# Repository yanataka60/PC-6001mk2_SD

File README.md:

# PC-6001mk2 MODE1～MODE4にSD-CARDからロード、セーブ機能

　PC-6001mk2の MODE1～MODE4でSD-CARDからロード、セーブ機能を実現するものです。

　対応機種は、PC-6001mk2、PC-6001mk2SR、PC-6601、PC-6601SRです。PC-6601、PC-6601SRはドライブ数切替スイッチは0として使ってください。

　対応しているCMT形式は、P6形式(拡張子はP6、CASのどちらでも大丈夫)とP6T形式です。

　CMTからの読み込み実行に数分掛かっていたゲームも数十秒で実行できます。

　なお、Arduino、ROMへ書き込むための機器が別途必要となります。

　また、本体内のBASIC-ROMを差し替えられるスキルがあればMODE5もSD対応にできます。詳細は、「MODE5対応について」を参照してください。

## 対応できないもの
　MODE1～MODE4については、BASIC-ROMを裏RAMにコピーしCMT関連ルーチンをSD-CARDアクセスに書き換えてSD-CARDへのアクセスを実現しています。

　MODE5についてはBASIC-ROMのCMT関連ルーチンにパッチを当てたROMに差し替えることでSD-CARDへのアクセスを実現していますが、MODE6についてはBASIC-ROMのCMT関連ルーチンが特定できていないためSD-CARDは使えません。

　また、BASIC-ROMのCMT関連ルーチンをコールせず独自ルーチンによりCMTからLOADするソフト（ロードランナー等）も対応できないので途中で止まります。

## 回路図
　KiCadフォルダ内のPC-6001mk2_SD.pdfを参照してください。

[回路図](https://github.com/yanataka60/PC-6001mk2_SD/blob/main/Kicad/PC-6001_mk2_SD.pdf)

## 部品
|番号|品名|数量|備考|
| ------------ | ------------ | ------------ | ------------ |
||J2、J3のいずれか(注1)|||
|J2|Micro_SD_Card_Kit|1|秋月電子通商 AE-microSD-LLCNV (注2)|
|J3|MicroSD Card Adapter|1|Arduino等に使われる5V電源に対応したもの (注4)|
|U1|74LS04|1||
|U2|74LS30|1||
|U4|8255|1||
|U5|2764/28C64相当品|1||
|U6|Arduino_Pro_Mini_5V|1|Atmega328版を使用 168版は不可。(注3)|
|C1 C2 C4 C5|積層セラミックコンデンサ 0.1uF|4||
|C6|電解コンデンサ 16v100uF|1||
||ピンヘッダ|2Pin分|Arduino_Pro_MiniにはA4、A5用のピンヘッダが付いていないため別途調達が必要です 秋月電子通商 PH-1x40SGなど|
||ピンソケット(任意)|26Pin分|Arduino_Pro_Miniを取り外し可能としたい場合に調達します 秋月電子通商 FHU-1x42SGなど|

　　　注1)J2又はJ3のどちらかを選択して取り付けてください。

　　　注2)秋月電子通商　AE-microSD-LLCNVのJ1ジャンパはショートしてください。

　　　注3)Arduino Pro MiniはA4、A5ピンも使っています。

　　　注4)MicroSD Card Adapterを使う場合

　　　　　J3に取り付けます。

　　　　　MicroSD Card Adapterについているピンヘッダを除去してハンダ付けするのが一番確実ですが、J3の穴にMicroSD Card Adapterをぴったりと押しつけ、裏から多めにハンダを流し込むことでハンダ付けをする方法もあります。なお、この方法の時にはしっかりハンダ付けが出来たかテスターで導通を確認しておいた方が安心です。

ハンダ付けに自信のない方はJ2の秋月電子通商　AE-microSD-LLCNVをお使いください。AE-microSD-LLCNVならパワーLED、アクセスLEDが付いています。

## ROMへの書込み
　Z80フォルダ内のEXT_ROM.binをROMライター(TL866II Plus等)を使って2764又は28C64に書き込みます。

## Arduinoプログラム
　Arduino IDEを使ってArduinoフォルダのPC-6001mk2_SDフォルダ内PC-6001mk2_SD.inoを書き込みます。

　SdFatライブラリを使用しているのでArduino IDEメニューのライブラリの管理からライブラリマネージャを立ち上げて「SdFat」をインストールしてください。

　「SdFat」で検索すれば見つかります。「SdFat」と「SdFat - Adafruit Fork」が見つかりますが「SdFat」のほうを使っています。

注)Arduinoを基板に直付けしている場合、Arduinoプログラムを書き込むときは、カートリッジスロットから抜き、74LS04を外したうえで書き込んでください。

## 接続
　カートリッジスロットに挿入します。

　カートリッジスロットへの抜き差しに基板のみでは不便です。

　STLフォルダに基板を載せられるトレイの3Dデータを置いたので出力して使うと便利です。

　PC-6601、PC-6601SRはドライブ数切替スイッチは0として使ってください。

## SD-CARD
　出来れば8GB以下のSDカードを用意してください。

　ArduinoのSdFatライブラリは、SD規格(最大2GB)、SDHC規格(2GB～32GB)に対応していますが、SDXC規格(32GB～2TB)には対応していません。

　また、SDHC規格のSDカードであっても32GB、16GBは相性により動作しないものがあるようです。

　FAT16又はFAT32が認識できます。NTFSは認識できません。

　ルートに置かれた拡張子が「.P6T」又は「.CAS」の形式ファイルのみ認識できます。(以外のファイル、フォルダも表示されますがLOAD実行の対象になりません)

　ファイル名は拡張子を除いて32文字まで、ただし半角カタカナ、及び一部の記号はArduinoが認識しないので使えません。パソコンでファイル名を付けるときはアルファベット、数字および空白でファイル名をつけてください。

　起動直後の画面は横32文字表示です。拡張子を含めて27文字以下にしたほうが画面の乱れません。

## 使い方

起動直後は拡張ROMのプログラムが走り、以下のコマンドが使えます。

### Launcherコマンド
#### 1から4までのいずれかの後に[CR]
次に「How Many Pages?(1-4)」と聞いてくるので画面数を入力すると入力された数字のMODEと画面数でSD対応にして起動します。

#### B[CR]
SD対応せずにBASICを起動します。

[STOP]キーと動作は同じです。

#### [STOP]キー
SD対応せずにBASICを起動します。

B[CR]と動作は同じです。

#### F[CR]又はF 文字列[CR]
文字列を入力せずにF[CR]のみ入力するとSD-CARDルートディレクトリにあるファイルの一覧を表示します。

文字列を付けて入力すればSD-CARDルートディレクトリにあるその文字列から始まるファイルの一覧を表示します。

10件表示したところで指示待ちになるので打ち切るならESC又は↑を入力すると打ち切られ、Bキーで前の10件に戻ります。それ以外のキーで次の10件を表示します。

　行頭に「*L 」を付加して表示してあるので実行したいファイルにカーソルキーを合わせて[CR]キーを押すだけでLOAD可能です。

　LOADの挙動については次のLコマンドの記述を参照してください。

　表示される順番は、登録順となりファイル名アルファベッド順などのソートした順で表示することはできません。

##### 例)
　　F[CR]

　　F S[CR]

　　F SP[CR]

#### L DOSファイル名[CR]
指定したDOSフィル名のファイルをSD-CARDからLOADします。

ファイル名の最後の「.P6T」「.CAS」は有っても無くても構いませんが、無い場合は「.P6T」が指定されたものとみなします。

　例)

　　L TEST.P6T -> DOSファイル名「TEST.P6T」を読み込みます。

　　L TEST.CAS -> DOSファイル名「TEST.CAS」を読み込みます。

　　L TEST -> DOSファイル名「TEST.P6T」を読み込みます。

　選択したファイルが「P6T」形式の場合、設定されたMODEと設定されたPagesで起動したうえで自動実行文字列を実行します。

　選択したファイルが「CAS」形式の場合、「Mode?(1-4)」と聞いてくるのでモードを入力、次に「How Many Pages?(1-4)」と聞いてくるので画面数を入力、最後に「Auto Run?(y/c/n)」と聞いてくるので「y」とすれば起動直後にCLOAD[CR]RUN[CR]が実行され、「c」とすればCLOAD[CR]だけが実行、「n」とすれば何も実行されません。

#### 操作上の注意
　~~「SD-CARD INITIALIZE ERROR」と表示されたときは、SD-CARDをいったん抜き再挿入したうえでArduinoをリセットしてください。~~

　~~SD-CARDにアクセスしていない時に電源が入ったままで SD-CARDを抜いた後、再挿入しSD-CARDにアクセスすると「SD-CARD INITIALIZE ERROR」となる場合があります。再挿入した場合にはSD-CARDにアクセスする前にArduinoを必ずリセットしてください。~~

　~~SD-CARDの抜き差しは電源を切った状態で行うほうがより確実です。~~

　(2024.3.12) SD-CARDにアクセスしていない時に電源が入ったままでSD-CARDを抜くと再度SD-CARDを挿入してもSD-CARDにアクセスできない問題を解消しました。(Arduinoを最新版に書き換えてください)

　再度SD-CARDを挿入した後、Fコマンド、Lコマンド、CLOAD、CSAVE等でSD-CARDに3回ほどアクセスすれば復旧します。

### BASICコマンド
#### CLOAD "DOSファイル名"[CR]
指定したDOSフィル名のBASICプログラムをSD-CARDからLOADします。

ファイル名は6文字以内で必須です。6文字以上入力された場合には7文字以降は無視されます。ファイル名を入力せずにCLOAD[CR]とすると暴走します。

ファイル名の前に"(ダブルコーテーション)は必須ですが、ファイル名の後ろに"(ダブルコーテーション)は有っても無くても構いません。

ファイル名の最後に「.CAS」は必要ありません。「.CAS」が指定されたものとみなします。

　例)

　　CLOAD "TEST" -> DOSファイル名「TEST.CAS」を読み込みます。

　　CLOAD "TESTTEST" -> DOSファイル名「TESTTE.CAS」を読み込みます。

　　CLOAD "TEST.BAS.CMT" -> DOSファイル名「TEST.BA.CMT」を読み込みます。

#### CSAVE "DOSファイル名"[CR]
BASICプログラムを指定したDOSフィル名でSD-CARDに上書きSAVEします。

ファイル名は6文字以内で必須です。6文字以上入力された場合には7文字以降は無視されます。

ファイル名の前に"(ダブルコーテーション)は必須ですが、ファイル名の後ろに"(ダブルコーテーション)は有っても無くても構いません。

ファイル名の最後の「.CAS」は必要ありません。「.CAS」が指定されたものとみなします。

　例)

　　CSAVE "TEST" -> 「TEST.CAS」で保存される。

　　CSAVE "TESTTEST" -> 「TESTTE.CAS」で保存される。

## MODE5対応について(本体BASIC-ROMの差し替えが必要です、自己責任でお願いします)
　MODE5では裏RAMが使われるため、「BASIC-ROMを裏RAMにコピーしCMT関連ルーチンをSD-CARDアクセスに書き換え」が出来ませんのでSD-CARDアクセス用にパッチを当てたBASIC-ROMに差し替えることでMODE5に対応します。

　なお、市販ソフトでは2段目以降のCMTロードはBASIC-ROMを使わずに独自のロードルーチンを使っているものがあり、動かないことが多いです。

　雑誌打ち込みプログラムのロード、セーブ用と割り切ってください。

　また、本体ROMの抜き差し等において本体が故障又はBASIC-ROMが破損しても当方では責任をとれませんので自己責任で行ってください。

　本体BASIC-ROMの本体内の位置及びROM内容の吸出しに関しても自分で解決できる方のみ挑戦願います。

#### 従来MONITORのRコマンド未対応としていましたが、最初に何らかのBASICプログラムが無いと正常に読み込めないのが原因です。
#### 月刊マイコン '85/11月号掲載「サブマリン606」のように最初にCLOAD、次にMON、R-0とするプログラムは正常に読み込めます。
#### 未確認ですが、機械語だけをR-0で読み込むプログラムも最初になんらかのBASICプログラム(10 clearだけでも)をくっつけたp6ファイルに修正すればR-0で読み込み、Gxxxxで実行できると思います。

### Arduinoプログラム
　ArduinoフォルダのPC-6001mk2_SDフォルダ内PC-6001mk2_SD.inoと同じもので動作します。

### ROMへの書込み
　Z80フォルダ内のEXT_ROM.binと同じもので動作します。

### BASIC-ROMへのパッチあて
　以下のアドレスを修正します。

|ADDRESS|修正前|修正後|
| ------------ | ------------ | ------------ |
|1A61|C5 D5 E5|C3 12 58|
|1A70|C5 D5 E5|C3 15 58|
|1AB8|C5 D5 E5|C3 18 58|
|1ACC|C5 D5 E5|C3 1B 58|
|1B06|C5 D5 E5|C3 1E 58|

　MODE5フォルダ内のROM_PATCH.binの内容で5812H～5A20Hまでを差し替えます。

　この差し替えによりfilesが使えなくなり、FDDを繋いでいない限り問題はないと思うのですが、何かしらのサブルーチンをつぶしてしまっているかもしれません。

　リセットが掛かってしまう等が起きるソフトのSD起動は取り敢えず諦めてください。

　出来上がったバイナリを27256等に焼いて本体内ICソケットにそのまま差し替えると、CMT、FDDが使えなくなってしまうので27512等にオリジナルバイナリを前半、パッチ済みバイナリを後半に置いて焼き、27512のA15を5VとGNDにスイッチで切り替えられるようにし、オリジナルバイナリとパッチ済みバイナリを切り替えて使ってください。

## 謝辞
　基板の作成に当たり以下のデータを使わせていただきました。ありがとうございました。

　Arduino Pro Mini

　　https://github.com/g200kg/kicad-lib-arduino

　AE-microSD-LLCNV

　　https://github.com/kuninet/PC-8001-SD-8kRAM

## 追記
　2022.10.26 SD-CARDに対応できないハード、ソフトについて加筆しました。

　　　　　　 FコマンドにもDI追加。

　2022.10.27 MODE5対応テストについて追記しました。

　2022.10.28 MODE5対応テストで不具合の出る可能性を追記しました。あくまでテストですので了承ください。

　2022.10.29 CMTload終了処理にCMTsave終了エントリをCallしているソフトへの対策をArduinoプログラムに追加。MODE5用と統合。

　　　　　　 MODE5対応テストにおいてMONITOR Rコマンドには未対応であることを追記。

　2022.10.31 MODE5対応用にBASIC-ROMを差し替えるときには27512を使うことを追記。

　　　　　　 U5 2764用プログラムのMODE1～MODE4用とMODE5用を統合。統合に伴ってArduinoプログラムも修正。BASIC-ROMの内容がオリジナルであればMODE1～MODE4用、修正されていればMODE1～MODE5用として動作。

　　　　　　 BASIC-ROMを差し替えていなければ2764、Arduinoとも更新の必要なし。

　2023. 3. 4 MODE5においてMONITOR Rコマンドが機能するためには、最初に何らかのBASICプログラムが必要であることを追記。

　　　　　　 AUTO STARTの選択肢をy/c/nとし、CLOADも実行しない選択を追加

　　　　　　 CLOAD、CSAVEがLOAD、SAVEと誤表記されていたものを修正

　2024.1.15 SDカードは8GB以下が望ましいことを追記。

　2024.3.12 電源が入ったままでSD-CARDを抜くと再度SD-CARDを挿入してもSD-CARDにアクセスできない問題を解消した。

　2025.3.20 P6形式が使えることが伝わりにくい表記を修正した。

　2025.3.29 ピーガー伝説➋代さんにご指摘いただいた「LBUFをRS232Cバッファ」に修正。ファイルリスト表示時にB(前頁表示)を押し続けると期待した動作をしない、basic起動時にキーを押しているとOUTコマンドが正常に発行されないという問題が解消されます。

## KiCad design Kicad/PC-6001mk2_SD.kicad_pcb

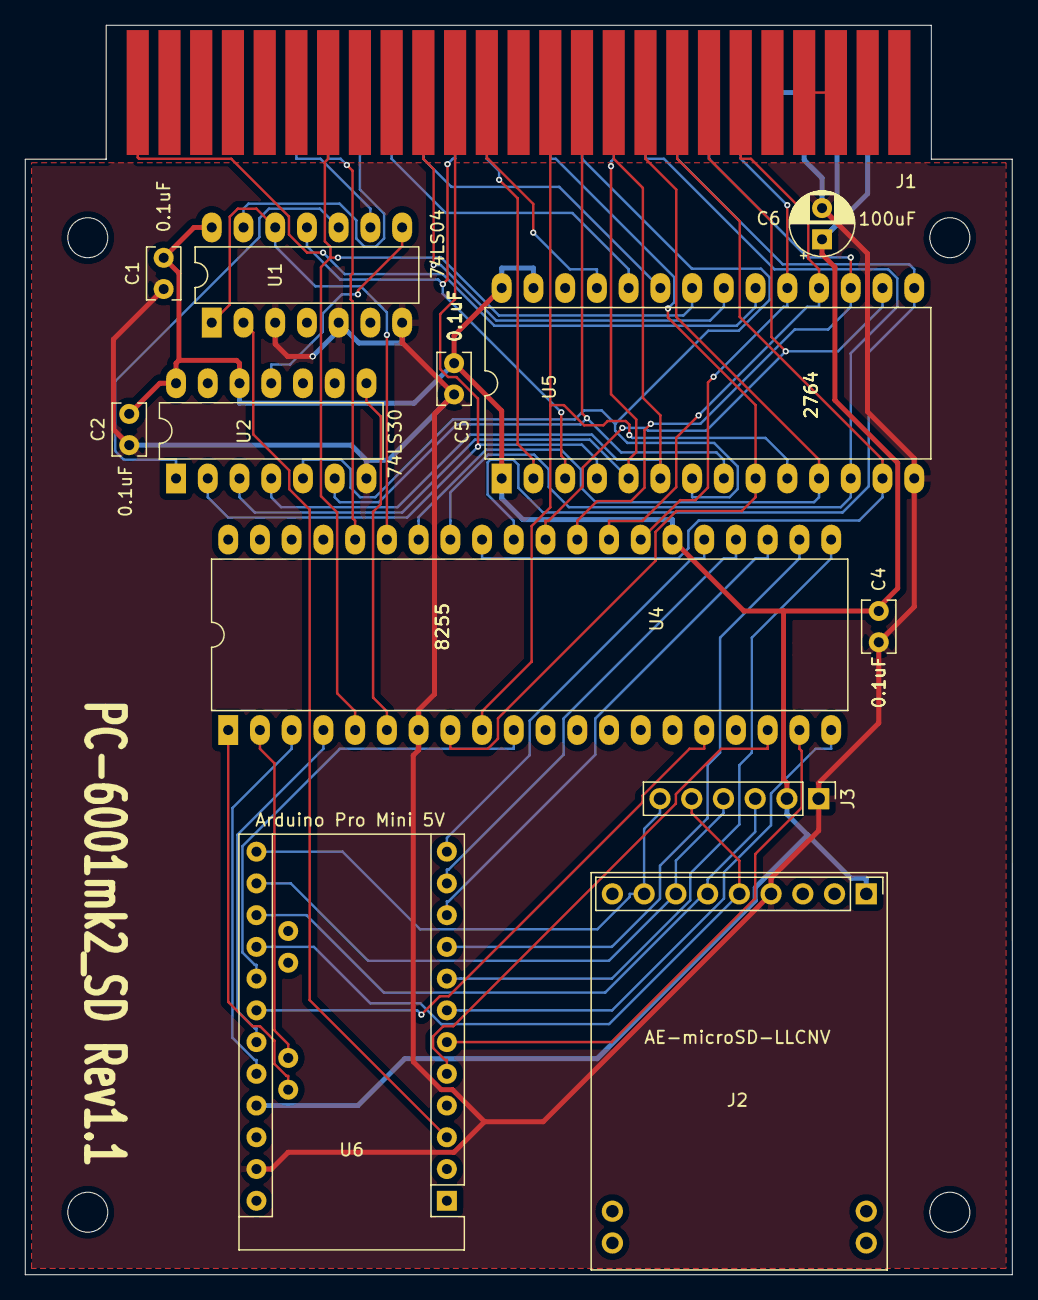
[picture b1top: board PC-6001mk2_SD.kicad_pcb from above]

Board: 2 copper layers, 79.0 x 100.0 mm, 17 parts (0 on the bottom side), 52 nets.

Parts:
C1, C2, C4, C5: 0.1uF; C_Rect_L4.0mm_W2.5mm_P2.50mm
C6: 100uF; CP_Radial_D5.0mm_P2.50mm
J1: PC-8001 BUS; BUS_50Pin
J2: Micro_SD_Card_Kit; AE-microSD-LLCNV
J3: MicroSD Card Adapter; PinHeader_1x06_P2.54mm_Vertical
MH1, MH2, MH3, MH4: MountingHole_3.2mm_M3
U1: 74LS04; DIP-14_W7.62mm_LongPads
U2: 74LS30; DIP-14_W7.62mm_LongPads
U4: 8255; DIP-40_W15.24mm_LongPads
U5: 2764; DIP-28_W15.24mm_LongPads
U6: Arduino_Pro_Mini_5V; Arduino_Pro_Mini

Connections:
+5V: C1.2, C2.2, C4.1, C5.1, C6.1, J1.45, J1.47, J2.1, J3.2, U1.14, U2.12, U2.14, U4.26, U5.1, U5.27, U5.28, U6.21
/A0: J1.28, U4.9, U5.10
/A1: J1.27, U4.8, U5.9
/A2: J1.30, U2.6, U5.8
/A3: J1.29, U2.5, U5.7
/A4: J1.32, U2.4, U5.6
/A5: J1.31, U2.3, U5.5
/A6: J1.22, U2.2, U5.4
/A7: J1.21, U1.11, U5.3
/A8: J1.24, U5.25
/A9: J1.17, U5.24
/A10: J1.20, U5.21
/A11: J1.19, U5.23
/A12: J1.23, U5.2
/CS: J2.8, J3.6, U6.13
/D0: J1.34, U4.34, U5.11
/D1: J1.33, U4.33, U5.12
/D2: J1.36, U4.32, U5.13
/D3: J1.35, U4.31, U5.15
/D4: J1.38, U4.30, U5.16
/D5: J1.37, U4.29, U5.17
/D6: J1.40, U4.28, U5.18
/D7: J1.39, U4.27, U5.19
/MISO: J2.6, J3.3, U6.15
/MOSI: J2.7, J3.4, U6.14
/MSW1: J1.44, J1.46
/SCK: J2.5, J3.5, U6.16
/~CS3: J1.2, U5.20
/~IORQ: J1.11, U1.9
/~RD: J1.14, U4.5, U5.22
/~RESET: J1.15, U1.13
/~WR: J1.13, U4.36
GND: C1.1, C2.1, C4.2, C5.2, C6.2, J1.41, J1.43, J2.4, J3.1, U1.3, U1.5, U1.7, U2.7, U4.7, U5.14, U6.23
unnamed: U1.1, U1.12, U4.35
unnamed: U1.2, U6.3
unnamed: U1.8, U2.11
unnamed: U1.10, U2.1
unnamed: U2.8, U4.6
unnamed: U4.1, U6.A5
unnamed: U4.2, U6.A4
unnamed: U4.3, U6.20
unnamed: U4.4, U6.19
unnamed: U4.10, U6.17
unnamed: U4.16, U6.18
unnamed: U4.18, U6.5
unnamed: U4.19, U6.6
unnamed: U4.20, U6.7
unnamed: U4.21, U6.8
unnamed: U4.22, U6.9
unnamed: U4.23, U6.10
unnamed: U4.24, U6.11
unnamed: U4.25, U6.12
